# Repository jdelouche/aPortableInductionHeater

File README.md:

# A Portable Induction Heater

## Description

This is a hardware design that can be used to create a portable induction heater.

The design uses a Texas Instrument C2000 Launchpad with a TMS320F28027 microcontroller and a full bridge MOSFET power stage. The MOSFETs are driven by the UCC27111 which are connected to the microcontroller enhanced PWM.

The power stage is managed through software with a high-frequency PWM ramp-up.

## Tools

* Kicad
* Git
* TI Code Composer Studio

Copyright (C) DELOUCHE-VILPOUX

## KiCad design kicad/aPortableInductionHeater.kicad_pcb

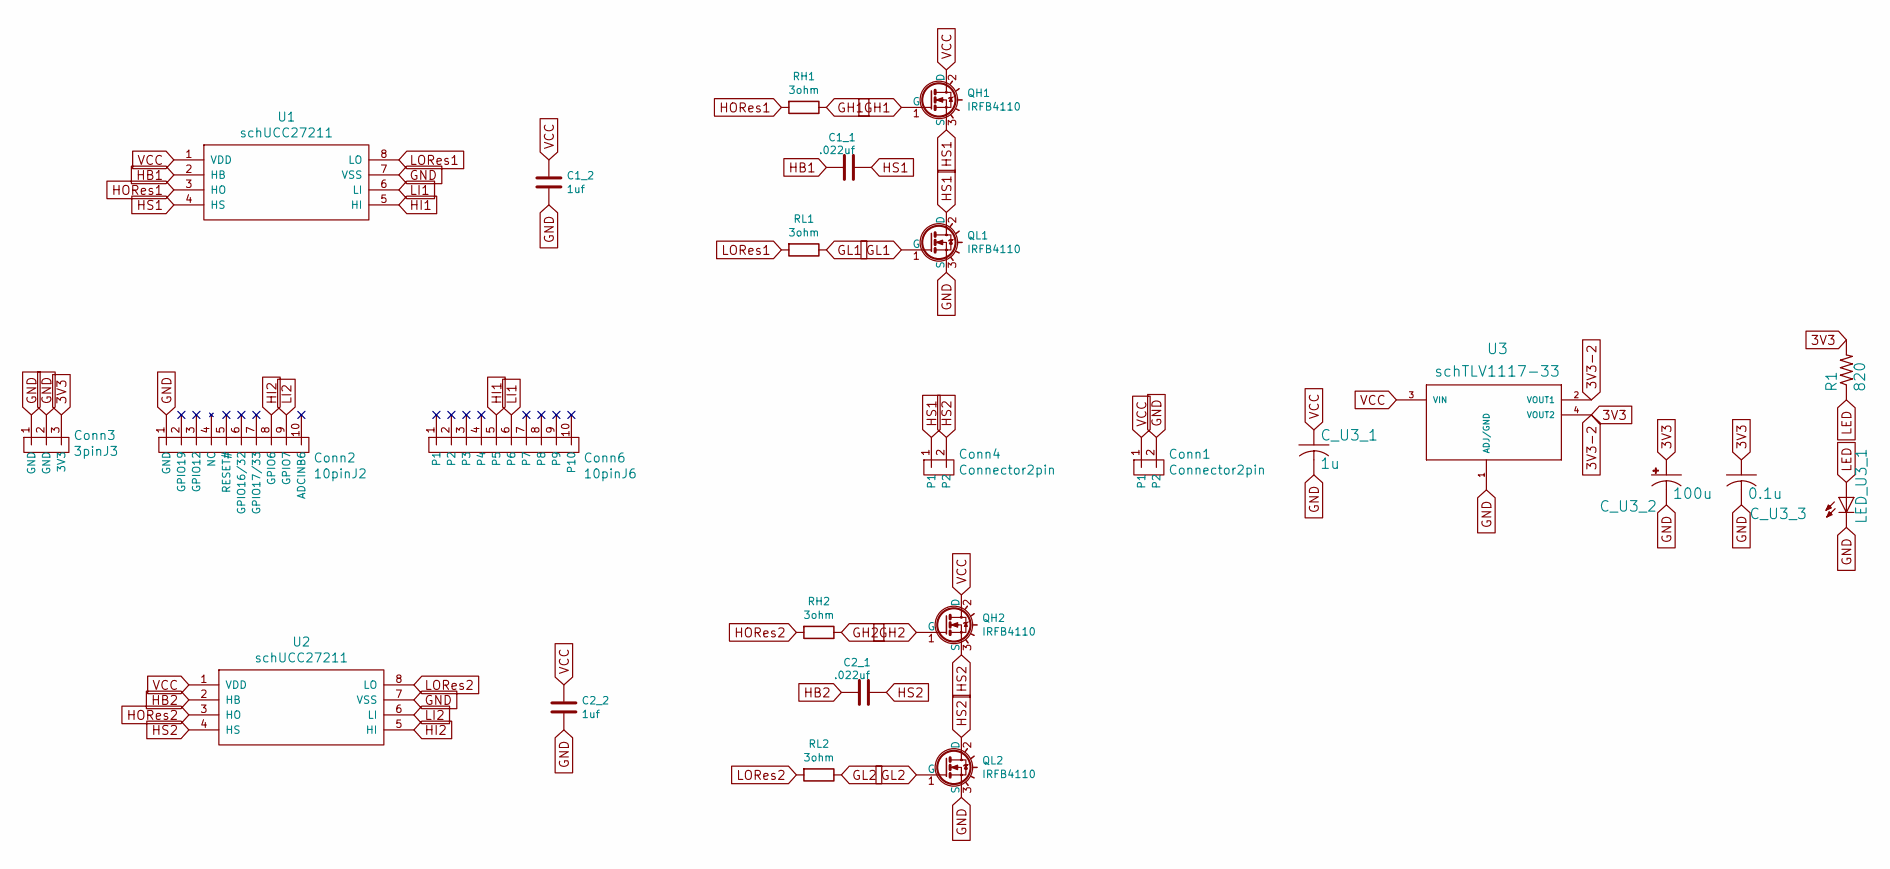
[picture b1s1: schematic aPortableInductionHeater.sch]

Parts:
C1_1, C2_1: .022uf; C_Rect_L11.0mm_W4.2mm_P10.00mm_MKT
C1_2, C2_2: 1uf; C_Rect_L18.0mm_W5.0mm_P15.00mm_FKS3_FKP3
C_U3_1: 1u; C_Rect_L10.0mm_W4.0mm_P7.50mm_MKS4
C_U3_2: 100u; CP_Radial_D10.0mm_P5.00mm
C_U3_3: 0.1u; C_Rect_L7.2mm_W3.5mm_P5.00mm_FKS2_FKP2_MKS2_MKP2
Conn1, Conn4: Connector2pin; bornier2
Conn2: 10pinJ2; MA10-1
Conn3: 3pinJ3; MA03-1
Conn6: 10pinJ6; MA10-1
LED_U3_1: LED_D5.0mm
QH1, QH2: IRFB4110; TO-220-HeatSinkHoles
QL1, QL2: IRFB4110; TO-220-HeatSinkHoles
R1: 820; R_Axial_DIN0204_L3.6mm_D1.6mm_P5.08mm_Horizontal
RH1, RH2: 3ohm; R_Axial_DIN0617_L17.0mm_D6.0mm_P20.32mm_Horizontal
RL1, RL2: 3ohm; R_Axial_DIN0617_L17.0mm_D6.0mm_P20.32mm_Horizontal
U1, U2: schUCC27211; UCC27211_SOIC-8_3.9x4.9mm_Pitch1.27mm
U3: schTLV1117-33; TEXAS_SOT223

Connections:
3V3: C_U3_2.1 (+), C_U3_3.1, Conn3.3 (3V3), R1.2, U3.2 (VOUT1), U3.4 (VOUT2)
GH1: QH1.1 (G), RH1.1
GH2: QH2.1 (G), RH2.1
GL1: QL1.1 (G), RL1.1
GL2: QL2.1 (G), RL2.1
GND: C1_2.2, C2_2.2, C_U3_1.2, C_U3_2.2 (-), C_U3_3.2, Conn1.2, Conn2.1 (GND), Conn3.1 (GND), Conn3.2 (GND), LED_U3_1.1 (C), QL1.3 (S), QL2.3 (S), U1.7 (VSS), U2.7 (VSS), U3.1 (ADJ/GND); also elsewhere on the board
HB1: C1_1.1, U1.2 (HB)
HB2: C2_1.1, U2.2 (HB)
HI1: Conn6.5, U1.5 (HI)
HI2: Conn2.8 (GPIO6), U2.5 (HI)
HORes1: RH1.2, U1.3 (HO)
HORes2: RH2.2, U2.3 (HO)
HS1: C1_1.2, Conn4.1, QH1.3 (S), QL1.2 (D), U1.4 (HS)
HS2: C2_1.2, Conn4.2, QH2.3 (S), QL2.2 (D), U2.4 (HS)
LED: LED_U3_1.2 (A), R1.1
LI1: Conn6.6, U1.6 (LI)
LI2: Conn2.9 (GPIO7), U2.6 (LI)
LORes1: RL1.2, U1.8 (LO)
LORes2: RL2.2, U2.8 (LO)
VCC: C1_2.1, C2_2.1, C_U3_1.1, Conn1.1, QH1.2 (D), QH2.2 (D), U1.1 (VDD), U2.1 (VDD), U3.3 (VIN)

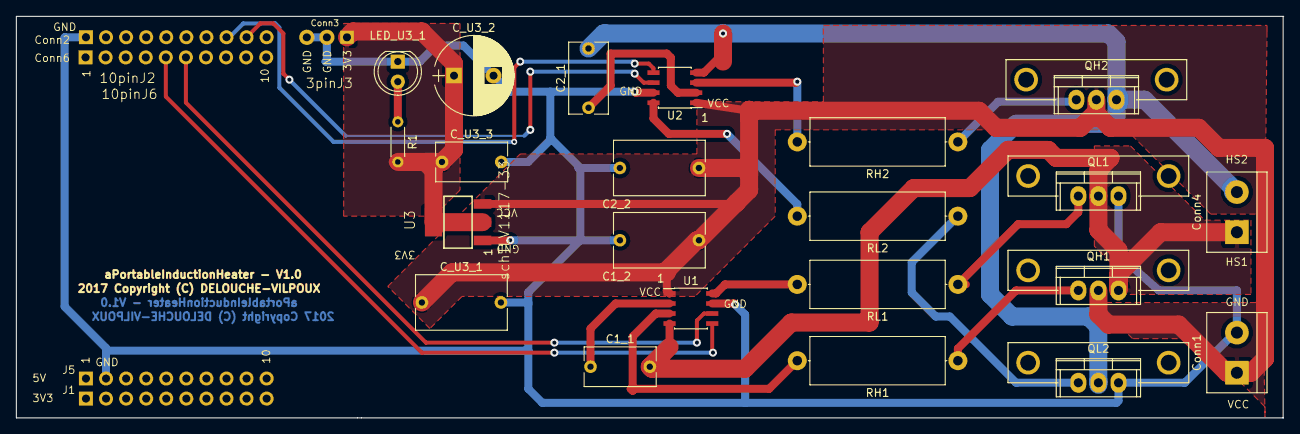
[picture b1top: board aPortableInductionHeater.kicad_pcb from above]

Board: 2 copper layers, 160.3 x 50.8 mm, 27 parts (0 on the bottom side), 20 nets.

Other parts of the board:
J1, J5: MA10-1

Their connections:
GND: J5.2; also elsewhere on the board

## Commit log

2017-05-11 Init
2017-05-11 Removed target
2017-05-11 changed fp IRFB4110
2017-05-12 Name&Version of the product
2017-05-13 v1.0
2017-05-13 2017
2017-05-13 Cartouche
2017-05-14 .zip

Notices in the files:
kicad/aPortableInductionHeater.kicad_pcb:
2017 Copyright (C) DELOUCHE-VILPOUX
